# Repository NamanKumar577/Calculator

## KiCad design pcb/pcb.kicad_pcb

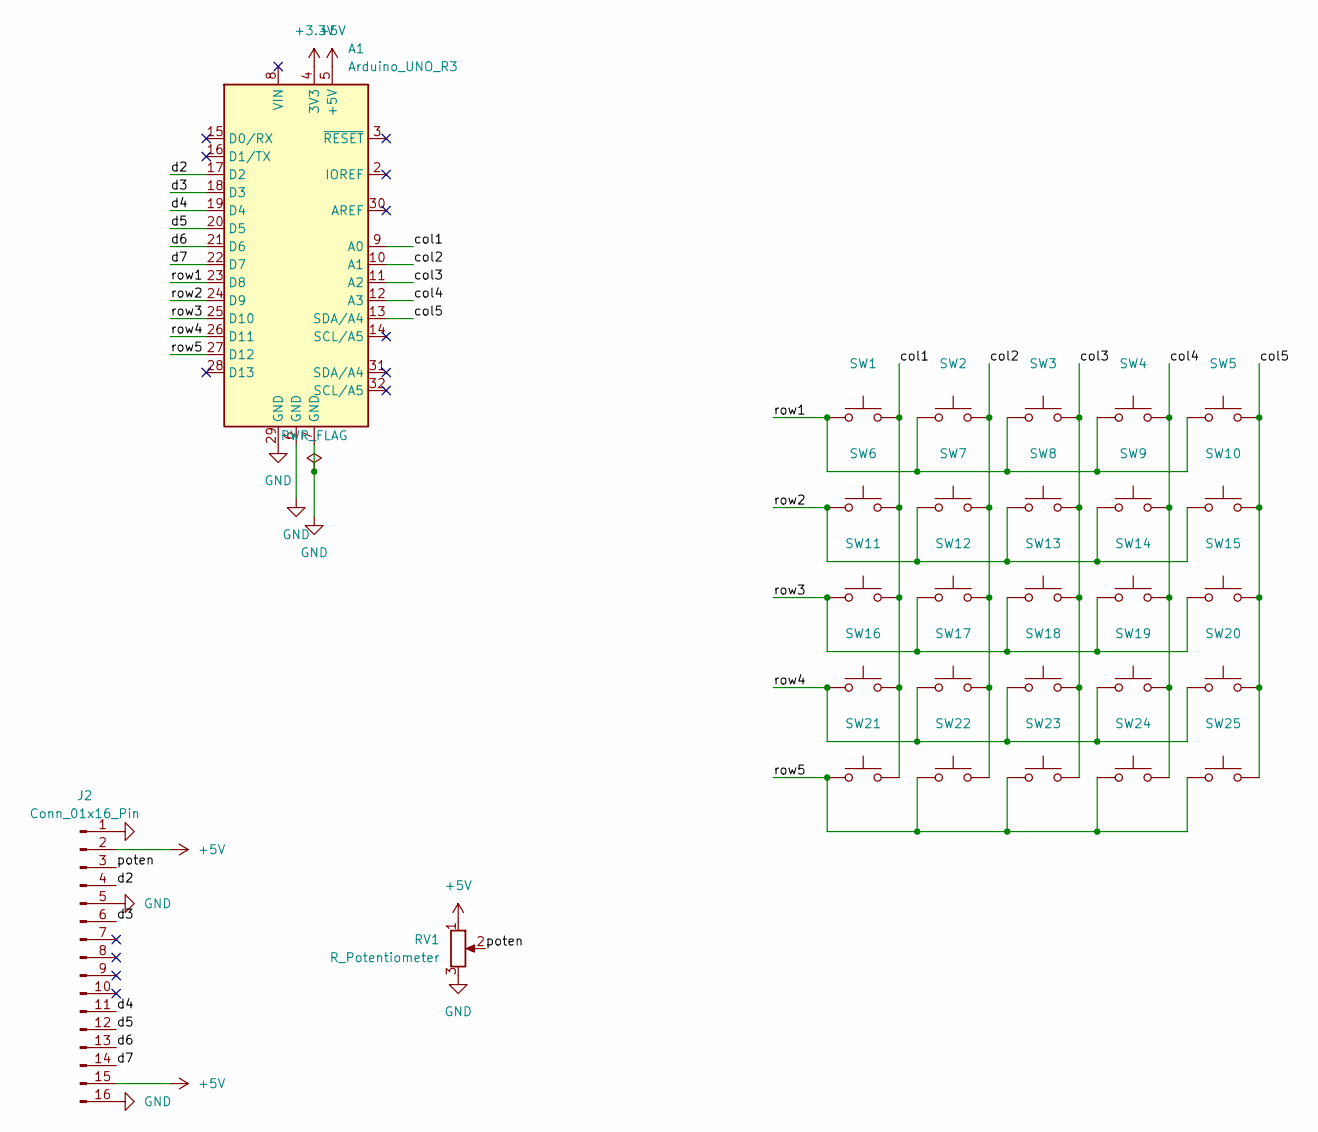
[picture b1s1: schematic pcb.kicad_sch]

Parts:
A1: Arduino_UNO_R3
J2: Conn_01x16_Pin; PinHeader_1x16_P2.54mm_Vertical
RV1: R_Potentiometer; Potentiometer_Alpha_RD901F-40-00D_Single_Vertical
SW1, SW2, SW3, SW4, SW5, SW6, SW7, SW8, SW9, SW10, SW11, SW12, SW13, SW14, SW15, SW16, SW17, SW18, SW19, SW20, SW21, SW22, SW23, SW24, SW25: SW_Push; SW_PUSH_6mm

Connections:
+3.3V: A1.4 (3V3)
+5V: A1.5 (+5V), J2.2, J2.15, RV1.1
/col1: A1.9 (A0), SW1.2, SW6.2, SW11.2, SW16.2, SW21.2
/col2: A1.10 (A1), SW2.2, SW7.2, SW12.2, SW17.2, SW22.2
/col3: A1.11 (A2), SW3.2, SW8.2, SW13.2, SW18.2, SW23.2
/col4: A1.12 (A3), SW4.2, SW9.2, SW14.2, SW19.2, SW24.2
/col5: A1.13 (SDA/A4), SW5.2, SW10.2, SW15.2, SW20.2, SW25.2
/d2: A1.17 (D2), J2.4
/d3: A1.18 (D3), J2.6
/d4: A1.19 (D4), J2.11
/d5: A1.20 (D5), J2.12
/d6: A1.21 (D6), J2.13
/d7: A1.22 (D7), J2.14
/poten: J2.3, RV1.2
/row1: A1.23 (D8), SW1.1, SW2.1, SW3.1, SW4.1, SW5.1
/row2: A1.24 (D9), SW6.1, SW7.1, SW8.1, SW9.1, SW10.1
/row3: A1.25 (D10), SW11.1, SW12.1, SW13.1, SW14.1, SW15.1
/row4: A1.26 (D11), SW16.1, SW17.1, SW18.1, SW19.1, SW20.1
/row5: A1.27 (D12), SW21.1, SW22.1, SW23.1, SW24.1, SW25.1
GND: A1.6 (GND), A1.7 (GND), A1.29 (GND), J2.1, J2.5, J2.16, RV1.3

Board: 2 copper layers, 28 parts (0 on the bottom side), 19 nets, no tracks yet.

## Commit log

2026-02-04 pcb 1
2026-02-04 Pcb schematic done
2026-02-04 sch with button
2026-02-04 pcb with button
2026-02-05 code
2026-02-05 server software
